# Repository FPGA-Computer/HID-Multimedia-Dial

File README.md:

HID Multimedia Dial

This is a USB HID with a rotatory encoder. This is used to supplement old keyboard layouts by providing a more natural alternative.

Details: https://hw-by-design.blogspot.com/2018/07/hid-multimedia-dial.html

USBasp Bootloader/  - bootloader used in this project configured for Atmel Studio 7.0

I use AVRDudess for programming.  Select USBasp as Programmer.
http://blog.zakkemble.co.uk/avrdudess-a-gui-for-avrdude/

Hardware/Main PCB/  - Eagle CAD files

Firmware/HID Descriptor Tool (DT)/ - report table file (.hid) for HID Descriptor Tool 
The tool is available at: http://www.usb.org/developers/hidpage/dt2_4.zip

Firmware/Atmel Studio 7 - Project files for the firmware

Licenses:

Firmware written by me are licensed under GPL v3.

Hardware is licensed under CC BY-4.0
https://creativecommons.org/licenses/by/4.0/

Additional incorporated code are under their own licenses.
- USBasp Bootloader by various authors is under GNU GPL v2
- V-USB by Christian Starkjohann is under GNU GPL v2, GPL v3

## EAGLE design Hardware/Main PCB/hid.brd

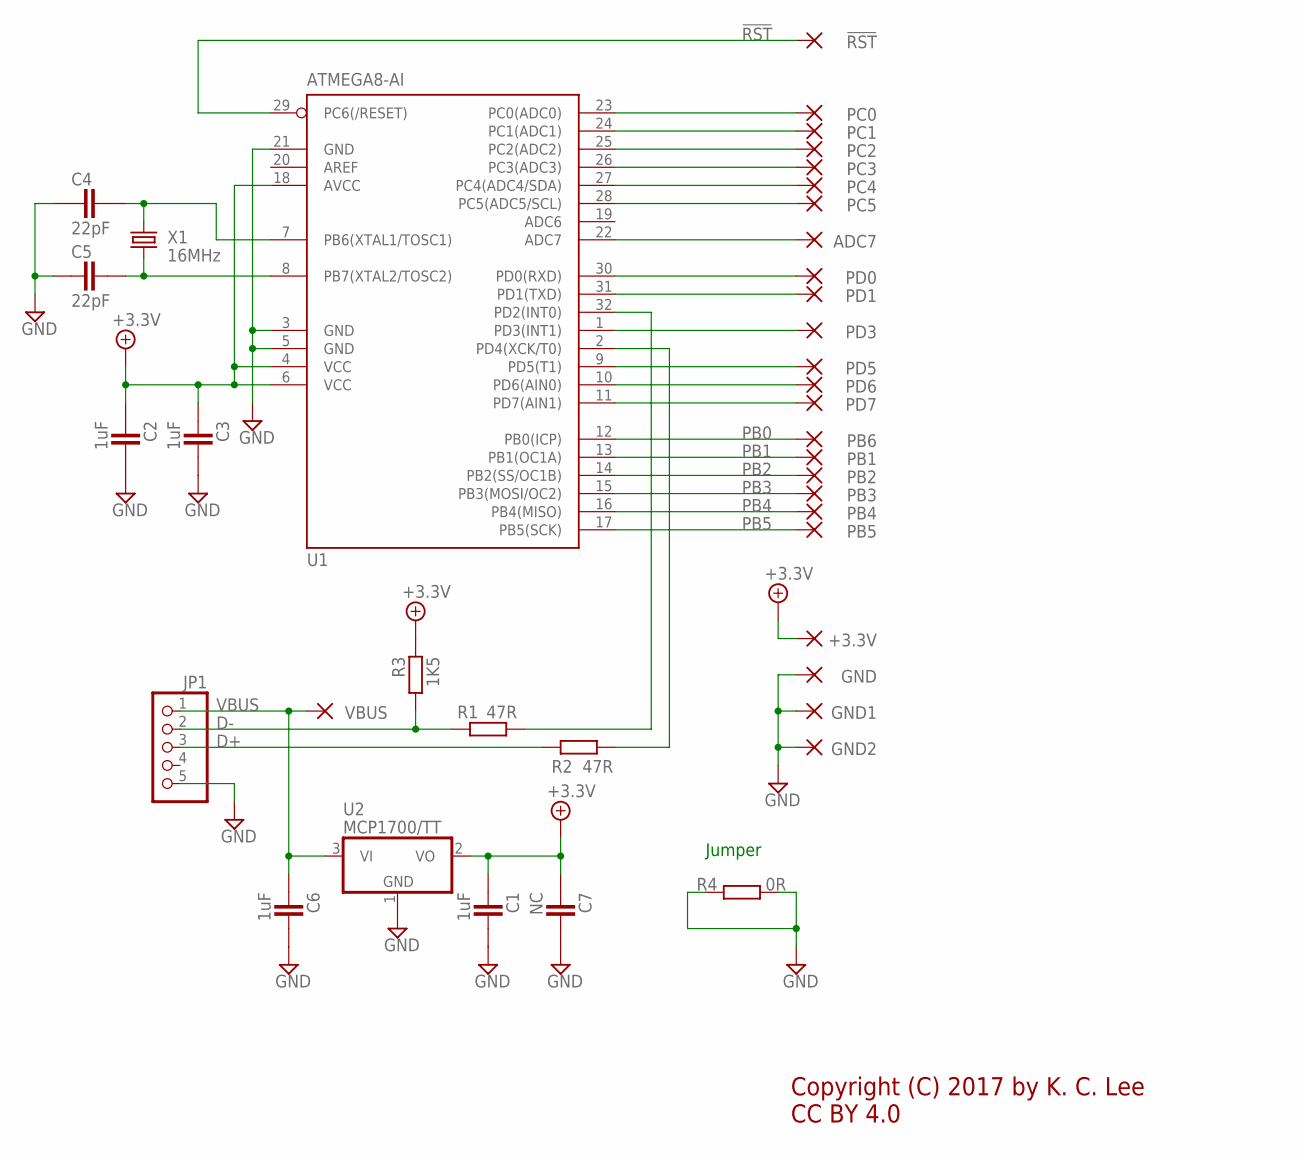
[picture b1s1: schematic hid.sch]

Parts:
!RST: SMD2; SMD1,27-2,54; PARTNO Breakout
+3.3V: SMD2; SMD1,27-2,54; PARTNO Breakout
ADC7: SMD2; SMD1,27-2,54; PARTNO Breakout
C1, C2, C3, C6: 1uF; CAPC1608X92N; PARTNO 1uF X7R 0603
C4, C5: 22pF; CAPC1608X92N; PARTNO 22pF 0603
C7: NC; CAPC2012X145AN; PARTNO NC 0805
GND, GND1, GND2: SMD2; SMD1,27-2,54; PARTNO Breakout
JP1: PINHD-1X5_2.54; 1X05; PARTNO *
PB1, PB2, PB3, PB4, PB5, PB6: SMD2; SMD1,27-2,54; PARTNO Breakout
PC0, PC1, PC2, PC3, PC4, PC5: SMD2; SMD1,27-2,54; PARTNO Breakout
PD0, PD1, PD3, PD5, PD6, PD7: SMD2; SMD1,27-2,54; PARTNO Breakout
R1, R2: 47R; RESC1608X55N; PARTNO 47R 0603
R3: 1K5; RESC1608X55N; PARTNO 1K5 0603
R4: 0R; RESC3115X70N; PARTNO 0R 1206
U1: ATMEGA8-AI; TQFP32-08; PARTNO ATmega8A-AU
U2: MCP1700/TT; SOT95P280X135-3N; PARTNO MCP1700T-3302E/TT
VBUS: SMD2; SMD1,27-2,54; PARTNO Breakout
X1: 16MHz; TC26H; PARTNO 16MHz Crystal TC26

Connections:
!RST: !RST.1, U1.29 (PC6(/RESET))
+3.3V: +3.3V.1, C1.1, C2.1, C3.1, C7.1, R3.1, U1.4 (VCC), U1.6 (VCC), U1.18 (AVCC), U2.2 (VO)
D2: R1.2, U1.32 (PD2(INT0))
D4: R2.2, U1.2 (PD4(XCK/T0))
D+: JP1.3, R2.1
D-: JP1.2, R1.1, R3.2
GND: C1.2, C2.2, C3.2, C4.1, C5.1, C6.2, C7.2, GND.1, GND1.1, GND2.1, JP1.5, R4.1, R4.2, U1.3 (GND), U1.5 (GND), U1.21 (GND), U2.1 (GND)
unnamed: PD7.1, U1.11 (PD7(AIN1))
unnamed: PD6.1, U1.10 (PD6(AIN0))
unnamed: PD5.1, U1.9 (PD5(T1))
unnamed: PD0.1, U1.30 (PD0(RXD))
unnamed: PD3.1, U1.1 (PD3(INT1))
unnamed: PD1.1, U1.31 (PD1(TXD))
unnamed: PC5.1, U1.28 (PC5(ADC5/SCL))
unnamed: PC4.1, U1.27 (PC4(ADC4/SDA))
unnamed: PC3.1, U1.26 (PC3(ADC3))
unnamed: PC2.1, U1.25 (PC2(ADC2))
unnamed: PC1.1, U1.24 (PC1(ADC1))
unnamed: PC0.1, U1.23 (PC0(ADC0))
unnamed: ADC7.1, U1.22 (ADC7)
unnamed: C4.2, U1.7 (PB6(XTAL1/TOSC1)), X1.1
unnamed: C5.2, U1.8 (PB7(XTAL2/TOSC2)), X1.2
PB0: PB6.1, U1.12 (PB0(ICP))
PB1: PB1.1, U1.13 (PB1(OC1A))
PB2: PB2.1, U1.14 (PB2(SS/OC1B))
PB3: PB3.1, U1.15 (PB3(MOSI/OC2))
PB4: PB4.1, U1.16 (PB4(MISO))
PB5: PB5.1, U1.17 (PB5(SCK))
VBUS: C6.1, JP1.1, U2.3 (VI), VBUS.1

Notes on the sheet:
Copyright (C) 2017 by K. C. Lee CC BY 4.0
Jumper

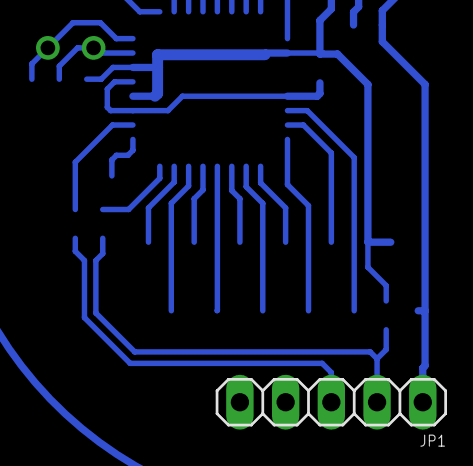
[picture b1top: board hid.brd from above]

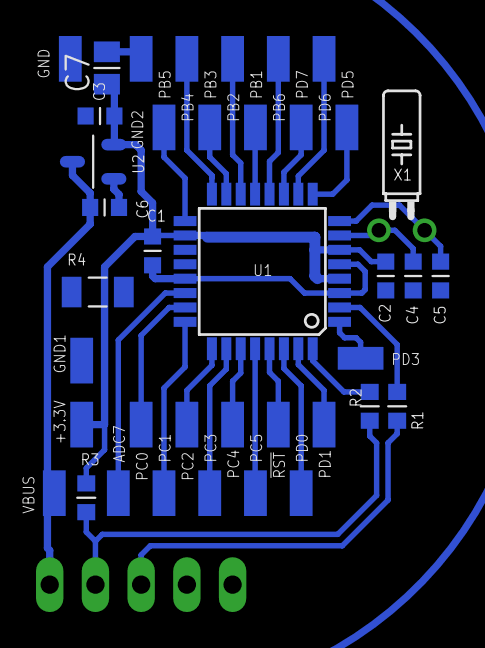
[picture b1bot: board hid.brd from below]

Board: 2 copper layers, 40 parts (39 on the bottom side), 29 nets.

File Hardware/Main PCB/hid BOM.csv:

"Qty","Value","Part Num","Package","Parts"
"1","","*","1X05","JP1"
"25","","BREAKOUT","SMD1,27-2,54","!RST, +3.3V, ADC7, GND, GND1, GND2, PB1, PB2, PB3, PB4, PB5, PB6, PC0, PC1, PC2, PC3, PC4, PC5, PD0, PD1, PD3, PD5, PD6, PD7, VBUS"
"1","0R","0R 1206","RESC3115X70N","R4"
"1","1K5","1K5 0603","RESC1608X55N","R3"
"4","1uF","1UF X7R 0603","CAPC1608X92N","C1, C2, C3, C6"
"1","16MHz","16MHZ CRYSTAL TC26","TC26H","X1"
"2","22pF","22PF 0603","CAPC1608X92N","C4, C5"
"2","47R","47R 0603","RESC1608X55N","R1, R2"
"1","ATMEGA8-AI","ATMEGA8A-AU","TQFP32-08","U1"
"1","MCP1700/TT","MCP1700T-3302E/TT","SOT95P280X135-3N","U2"
"1","NC","NC 0805","CAPC2012X145AN","C7"

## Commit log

2017-08-29 USBasp bootloader
2017-08-30 Main PCB
2017-08-30 hardware updates
2017-09-01 Firmware release
2017-09-01 Clean up, license and name change
2017-09-01 compiled version
2017-09-01 Fuse settings
2018-07-26 Change to blogger.com for my host.
